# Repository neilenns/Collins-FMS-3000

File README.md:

# Collins-FMS-3000
PCB for a replica Collins FMS-3000 to use with MobiFlight

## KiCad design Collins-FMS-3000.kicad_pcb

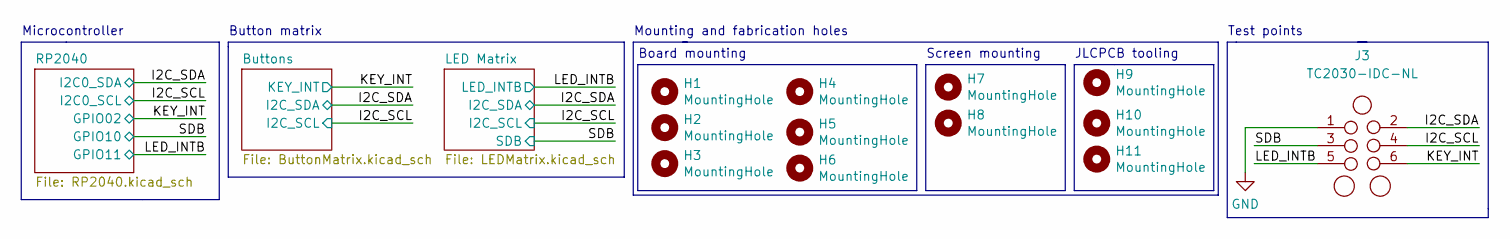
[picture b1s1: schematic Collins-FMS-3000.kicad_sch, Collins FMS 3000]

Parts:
H1, H2, H3, H4, H5, H6, H7, H8: MountingHole; MountingHole_3.2mm_M3
H9, H10, H11: MountingHole; JLCPCB_Tooling_Hole
J3: TC2030-IDC-NL; Tag-Connect_TC2030-IDC-NL_2x03_P1.27mm_Vertical

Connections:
/I2C_SCL: J3.4; also elsewhere on the board
/I2C_SDA: J3.2; also elsewhere on the board
/KEY_INT: J3.6; also elsewhere on the board
/LED_INTB: J3.5; also elsewhere on the board
/SDB: J3.3; also elsewhere on the board
GND: J3.1; also elsewhere on the board

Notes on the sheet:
Test points
Button matrix
Board mounting
Screen mounting
Microcontroller
Mounting and fabrication holes
JLCPCB tooling

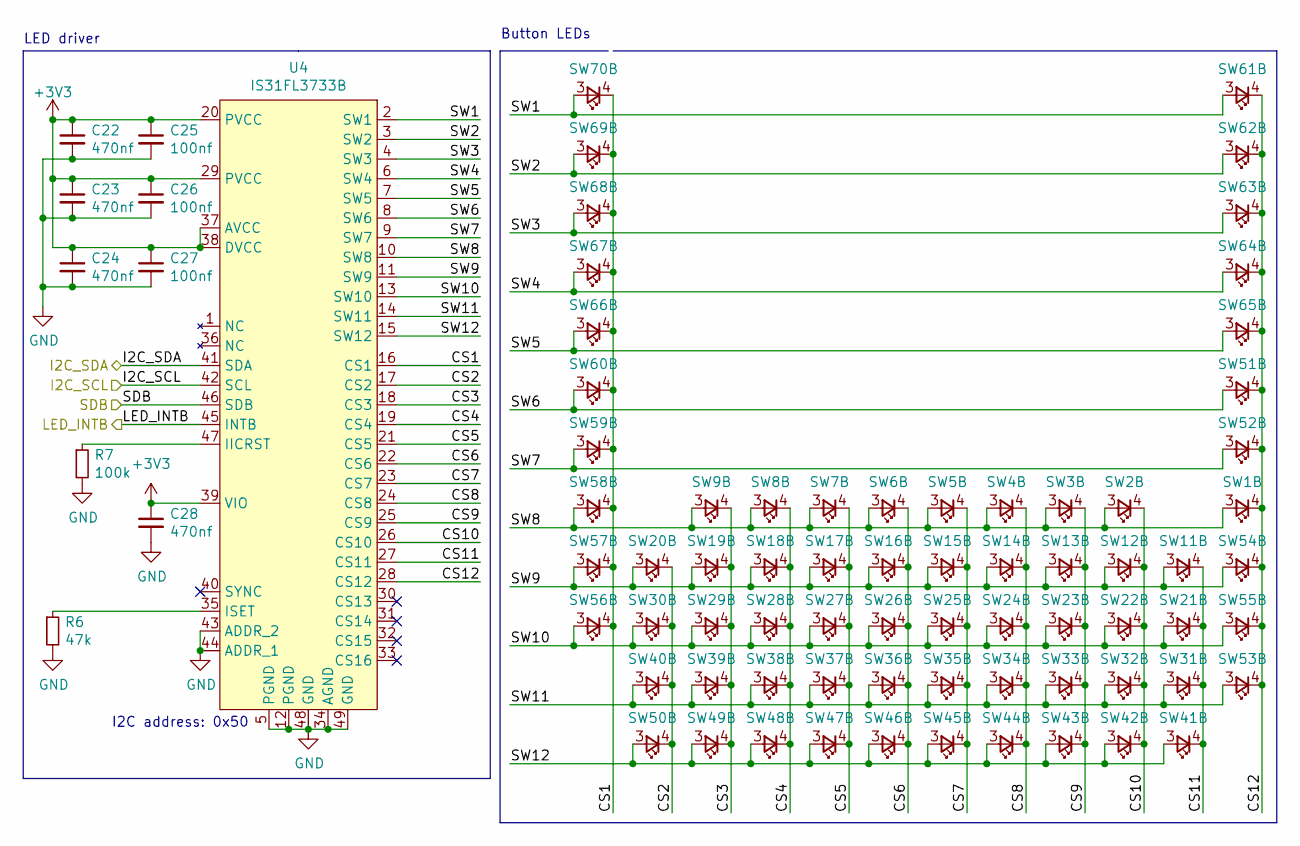
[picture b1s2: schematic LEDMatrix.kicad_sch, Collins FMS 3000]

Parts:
C22, C23, C24, C28: 470nf; Perfect_0402; MPN - JLCPCB C47339; JLC 0402
C25, C26, C27: 100nf; Perfect_0402; MPN - JLCPCB C1525; JLC 0402
R6: 47k; Perfect_0402; MPN - JLCPCB C25792; JLC 0402
R7: 100k; R_0603_1608Metric; MPN - JLCPCB C25803; JLC 0603
SW1, SW2, SW3, SW4, SW5, SW6, SW7, SW8, SW9, SW11, SW12, SW13, SW14, SW15, SW16, SW17, SW18, SW19, SW20, SW21, SW22, SW23, SW24, SW25, SW26, SW27, SW28, SW29, SW30, SW31, SW32, SW33, SW34, SW35, SW36, SW37, SW38, SW39, SW40, SW41, SW42, SW43, SW44, SW45, SW46, SW47, SW48, SW49, SW50, SW51, SW52, SW53, SW54, SW55, SW56, SW57, SW58, SW59, SW60, SW61, SW62, SW63, SW64, SW65, SW66, SW67, SW68, SW69, SW70: SW_Push_LED; SW_PUSH_LED_THT
U4: IS31FL3733B; TQFP-48-1EP_7x7mm_P0.5mm_EP5x5mm_ThermalVias

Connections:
+3V3: C22.1, C23.1, C24.1, C25.1, C26.1, C27.1, C28.1, U4.20 (PVCC), U4.29 (PVCC), U4.37 (AVCC), U4.38 (DVCC), U4.39 (VIO); also elsewhere on the board
/I2C_SCL: U4.42 (SCL); also elsewhere on the board
/I2C_SDA: U4.41 (SDA); also elsewhere on the board
/LED Matrix/CS1: SW56.4, SW57.4, SW58.4, SW59.4, SW60.4, SW66.4, SW67.4, SW68.4, SW69.4, SW70.4, U4.16 (CS1)
/LED Matrix/CS2: SW20.4, SW30.4, SW40.4, SW50.4, U4.17 (CS2)
/LED Matrix/CS3: SW9.4, SW19.4, SW29.4, SW39.4, SW49.4, U4.18 (CS3)
/LED Matrix/CS4: SW8.4, SW18.4, SW28.4, SW38.4, SW48.4, U4.19 (CS4)
/LED Matrix/CS5: SW7.4, SW17.4, SW27.4, SW37.4, SW47.4, U4.21 (CS5)
/LED Matrix/CS6: SW6.4, SW16.4, SW26.4, SW36.4, SW46.4, U4.22 (CS6)
/LED Matrix/CS7: SW5.4, SW15.4, SW25.4, SW35.4, SW45.4, U4.23 (CS7)
/LED Matrix/CS8: SW4.4, SW14.4, SW24.4, SW34.4, SW44.4, U4.24 (CS8)
/LED Matrix/CS9: SW3.4, SW13.4, SW23.4, SW33.4, SW43.4, U4.25 (CS9)
/LED Matrix/CS10: SW2.4, SW12.4, SW22.4, SW32.4, SW42.4, U4.26 (CS10)
/LED Matrix/CS11: SW11.4, SW21.4, SW31.4, SW41.4, U4.27 (CS11)
/LED Matrix/CS12: SW1.4, SW51.4, SW52.4, SW53.4, SW54.4, SW55.4, SW61.4, SW62.4, SW63.4, SW64.4, SW65.4, U4.28 (CS12)
/LED Matrix/SW1: SW61.3, SW70.3, U4.2 (SW1)
/LED Matrix/SW2: SW62.3, SW69.3, U4.3 (SW2)
/LED Matrix/SW3: SW63.3, SW68.3, U4.4 (SW3)
/LED Matrix/SW4: SW64.3, SW67.3, U4.6 (SW4)
/LED Matrix/SW5: SW65.3, SW66.3, U4.7 (SW5)
/LED Matrix/SW6: SW51.3, SW60.3, U4.8 (SW6)
/LED Matrix/SW7: SW52.3, SW59.3, U4.9 (SW7)
/LED Matrix/SW8: SW1.3, SW2.3, SW3.3, SW4.3, SW5.3, SW6.3, SW7.3, SW8.3, SW9.3, SW58.3, U4.10 (SW8)
/LED Matrix/SW9: SW11.3, SW12.3, SW13.3, SW14.3, SW15.3, SW16.3, SW17.3, SW18.3, SW19.3, SW20.3, SW54.3, SW57.3, U4.11 (SW9)
/LED Matrix/SW10: SW21.3, SW22.3, SW23.3, SW24.3, SW25.3, SW26.3, SW27.3, SW28.3, SW29.3, SW30.3, SW55.3, SW56.3, U4.13 (SW10)
/LED Matrix/SW11: SW31.3, SW32.3, SW33.3, SW34.3, SW35.3, SW36.3, SW37.3, SW38.3, SW39.3, SW40.3, SW53.3, U4.14 (SW11)
/LED Matrix/SW12: SW41.3, SW42.3, SW43.3, SW44.3, SW45.3, SW46.3, SW47.3, SW48.3, SW49.3, SW50.3, U4.15 (SW12)
/LED_INTB: U4.45 (INTB); also elsewhere on the board
/SDB: U4.46 (SDB); also elsewhere on the board
GND: C22.2, C23.2, C24.2, C25.2, C26.2, C27.2, C28.2, R6.2, R7.2, U4.5 (PGND), U4.12 (PGND), U4.34 (AGND), U4.43 (ADDR_2), U4.44 (ADDR_1), U4.48 (GND), U4.49 (GND); also elsewhere on the board
unnamed: R6.1, U4.35 (ISET)
unnamed: R7.1, U4.47 (IICRST)

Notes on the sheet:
LED driver
I2C address: 0x50
Button LEDs

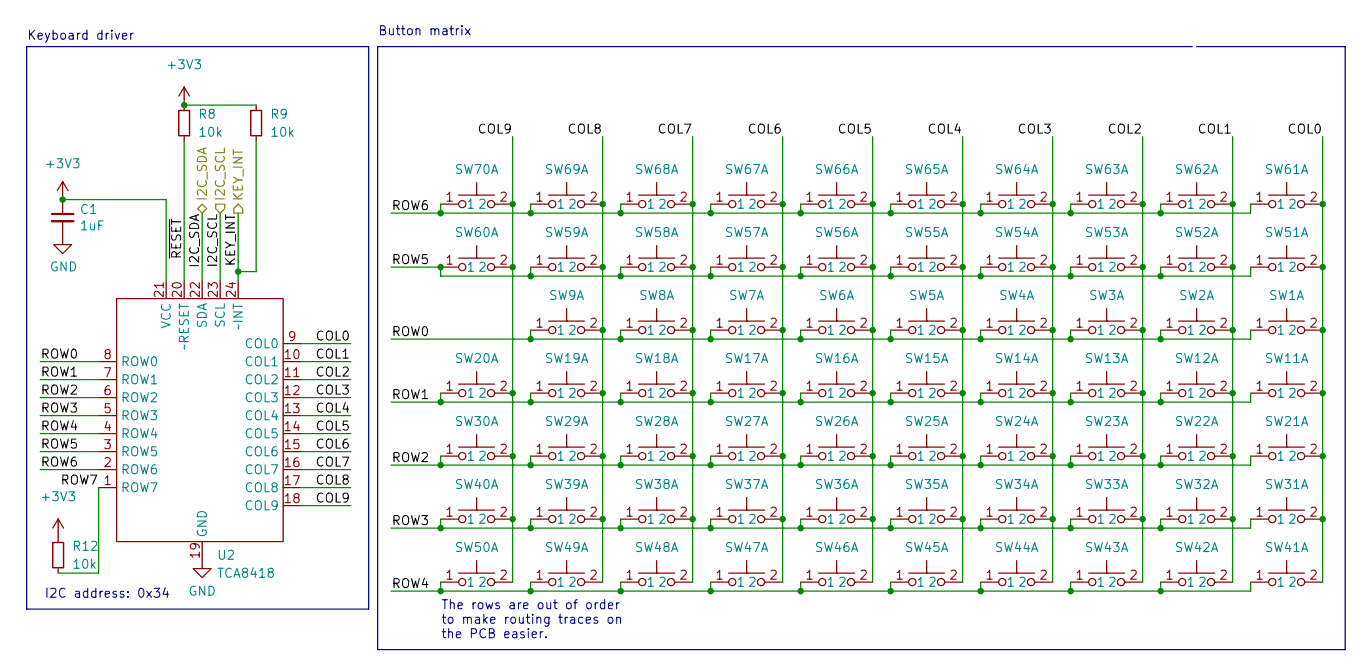
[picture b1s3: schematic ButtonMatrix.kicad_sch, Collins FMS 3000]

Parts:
C1: 1uF; Perfect_0402; MPN - JLCPCB C52923; JLC 0402
R8, R9, R12: 10k; Perfect_0402; MPN - JLCPCB C25744
SW1, SW2, SW3, SW4, SW5, SW6, SW7, SW8, SW9, SW11, SW12, SW13, SW14, SW15, SW16, SW17, SW18, SW19, SW20, SW21, SW22, SW23, SW24, SW25, SW26, SW27, SW28, SW29, SW30, SW31, SW32, SW33, SW34, SW35, SW36, SW37, SW38, SW39, SW40, SW41, SW42, SW43, SW44, SW45, SW46, SW47, SW48, SW49, SW50, SW51, SW52, SW53, SW54, SW55, SW56, SW57, SW58, SW59, SW60, SW61, SW62, SW63, SW64, SW65, SW66, SW67, SW68, SW69, SW70: SW_Push_LED; SW_PUSH_LED_THT
U2: TCA8418; WQFN-24-1EP_4x4mm_P0.5mm_EP2.6x2.6mm; MPN - JLCPCB C138713

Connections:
+3V3: C1.1, R8.1, R9.1, R12.1, U2.21 (VCC); also elsewhere on the board
/Buttons/COL0: SW1.2, SW11.2, SW21.2, SW31.2, SW41.2, SW51.2, SW61.2, U2.9 (COL0)
/Buttons/COL1: SW2.2, SW12.2, SW22.2, SW32.2, SW42.2, SW52.2, SW62.2, U2.10 (COL1)
/Buttons/COL2: SW3.2, SW13.2, SW23.2, SW33.2, SW43.2, SW53.2, SW63.2, U2.11 (COL2)
/Buttons/COL3: SW4.2, SW14.2, SW24.2, SW34.2, SW44.2, SW54.2, SW64.2, U2.12 (COL3)
/Buttons/COL4: SW5.2, SW15.2, SW25.2, SW35.2, SW45.2, SW55.2, SW65.2, U2.13 (COL4)
/Buttons/COL5: SW6.2, SW16.2, SW26.2, SW36.2, SW46.2, SW56.2, SW66.2, U2.14 (COL5)
/Buttons/COL6: SW7.2, SW17.2, SW27.2, SW37.2, SW47.2, SW57.2, SW67.2, U2.15 (COL6)
/Buttons/COL7: SW8.2, SW18.2, SW28.2, SW38.2, SW48.2, SW58.2, SW68.2, U2.16 (COL7)
/Buttons/COL8: SW9.2, SW19.2, SW29.2, SW39.2, SW49.2, SW59.2, SW69.2, U2.17 (COL8)
/Buttons/COL9: SW20.2, SW30.2, SW40.2, SW50.2, SW60.2, SW70.2, U2.18 (COL9)
/Buttons/ROW0: SW1.1, SW2.1, SW3.1, SW4.1, SW5.1, SW6.1, SW7.1, SW8.1, SW9.1, U2.8 (ROW0)
/Buttons/ROW1: SW11.1, SW12.1, SW13.1, SW14.1, SW15.1, SW16.1, SW17.1, SW18.1, SW19.1, SW20.1, U2.7 (ROW1)
/Buttons/ROW2: SW21.1, SW22.1, SW23.1, SW24.1, SW25.1, SW26.1, SW27.1, SW28.1, SW29.1, SW30.1, U2.6 (ROW2)
/Buttons/ROW3: SW31.1, SW32.1, SW33.1, SW34.1, SW35.1, SW36.1, SW37.1, SW38.1, SW39.1, SW40.1, U2.5 (ROW3)
/Buttons/ROW4: SW41.1, SW42.1, SW43.1, SW44.1, SW45.1, SW46.1, SW47.1, SW48.1, SW49.1, SW50.1, U2.4 (ROW4)
/Buttons/ROW5: SW51.1, SW52.1, SW53.1, SW54.1, SW55.1, SW56.1, SW57.1, SW58.1, SW59.1, SW60.1, U2.3 (ROW5)
/Buttons/ROW6: SW61.1, SW62.1, SW63.1, SW64.1, SW65.1, SW66.1, SW67.1, SW68.1, SW69.1, SW70.1, U2.2 (ROW6)
/Buttons/ROW7: R12.2, U2.1 (ROW7)
/Buttons/~RESET: R8.2, U2.20 (~RESET)
/I2C_SCL: U2.23 (SCL); also elsewhere on the board
/I2C_SDA: U2.22 (SDA); also elsewhere on the board
/KEY_INT: R9.2, U2.24 (~INT); also elsewhere on the board
GND: C1.2, U2.19 (GND); also elsewhere on the board

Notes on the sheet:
The rows are out of order to make routing traces on the PCB easier.
Button matrix
Keyboard driver
I2C address: 0x34

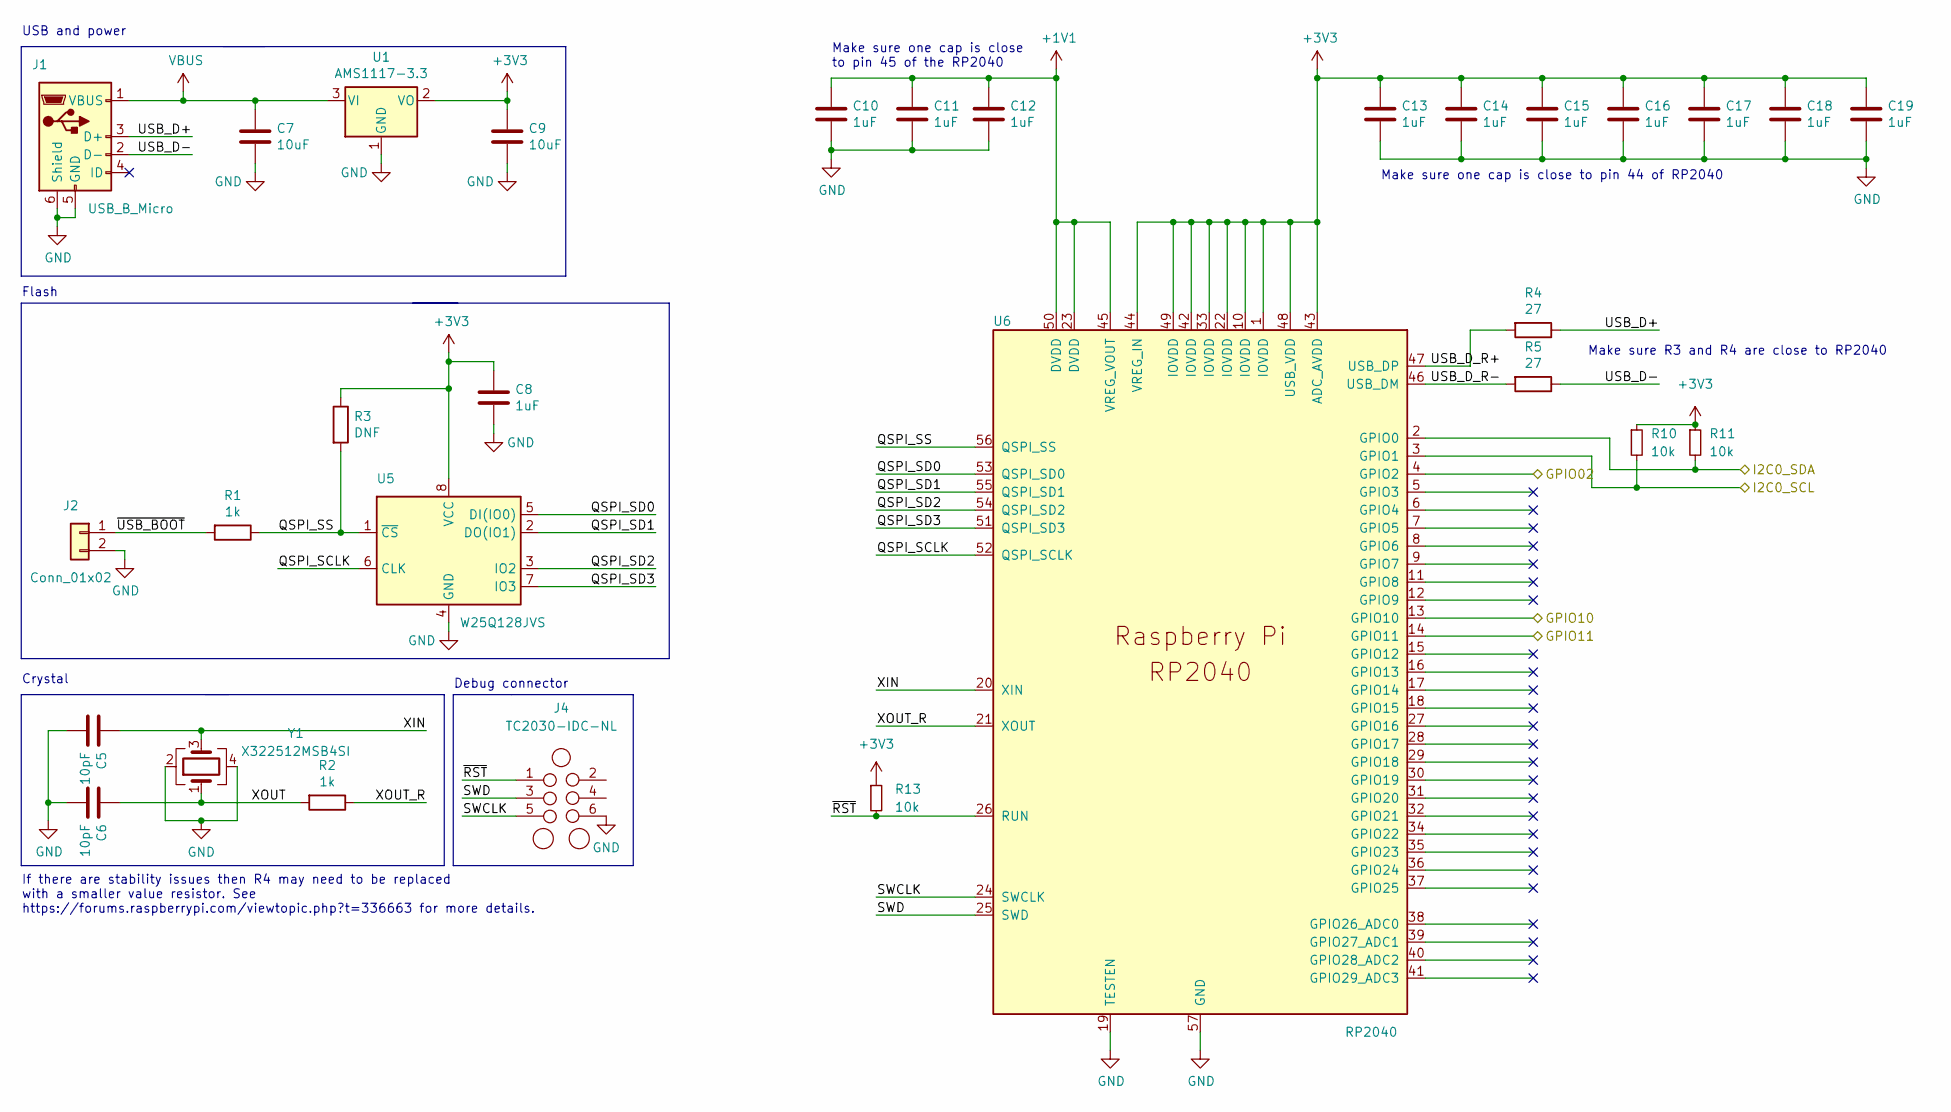
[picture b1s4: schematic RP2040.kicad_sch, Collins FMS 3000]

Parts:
C5, C6: 10pF; Perfect_0402; MPN - JLCPCB C32949; JLC 0402
C7, C9: 10uF; C_0603_1608Metric; MPN - JLCPCB C19702; JLC 0603
C8, C10, C11, C12, C13, C14, C15, C16, C17, C18, C19: 1uF; Perfect_0402; MPN - JLCPCB C52923; JLC 0402
J1: USB_B_Micro; USB_B_Mini_Amphenol_UE25BE5510H
J2: Conn_01x02; PinHeader_1x02_P2.54mm_Vertical
J4: TC2030-IDC-NL; Tag-Connect_TC2030-IDC-NL_2x03_P1.27mm_Vertical
R1, R2: 1k; Perfect_0402; MPN - JLCPCB C11702; JLC 0402
R3: DNF; R_1206_3216Metric_Pad1.30x1.75mm_HandSolder
R4, R5: 27; R_0603_1608Metric; MPN - JLCPCB C25190; JLC 0603
R10, R11: 10k; R_1206_3216Metric_Pad1.30x1.75mm_HandSolder; MPN - JLCPCB C17902
R13: 10k; Perfect_0402; MPN - JLCPCB C25744
U1: AMS1117-3.3; SOT-223-3_TabPin2; MPN - JLCPCB C6186; JLC SOT-223
U5: W25Q128JVS; SOIC-8_5.23x5.23mm_P1.27mm; MPN - JLCPCB C97521; JLC SOIC-8_5.3x5.3x1.27P
U6: RP2040; QFN56P40_700X700X90L40X18T310N; MPN - JLCPCB C2040; JLC LQFN-56_EP_7.0x7.0x0.4P
Y1: X322512MSB4SI; Crystal_SMD_3225-4Pin_3.2x2.5mm; MPN - JLCPCB C9002; JLC SMD-3225_4P

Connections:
+1V1: C10.1, C11.1, C12.1, U6.23 (DVDD), U6.45 (VREG_VOUT), U6.50 (DVDD)
+3V3: C8.1, C9.1, C13.1, C14.1, C15.1, C16.1, C17.1, C18.1, C19.1, R3.1, R10.1, R11.1, R13.1, U1.2 (VO), U5.8 (VCC), U6.1 (IOVDD), U6.10 (IOVDD), U6.22 (IOVDD), U6.33 (IOVDD), U6.42 (IOVDD), U6.43 (ADC_AVDD), U6.44 (VREG_IN), U6.48 (USB_VDD), U6.49 (IOVDD); also elsewhere on the board
/I2C_SCL: R10.2, U6.3 (GPIO1); also elsewhere on the board
/I2C_SDA: R11.2, U6.2 (GPIO0); also elsewhere on the board
/KEY_INT: U6.4 (GPIO2); also elsewhere on the board
/LED_INTB: U6.14 (GPIO11); also elsewhere on the board
/RP2040/QSPI_SCLK: U5.6 (CLK), U6.52 (QSPI_SCLK)
/RP2040/QSPI_SD0: U5.5 (DI(IO0)), U6.53 (QSPI_SD0)
/RP2040/QSPI_SD1: U5.2 (DO(IO1)), U6.55 (QSPI_SD1)
/RP2040/QSPI_SD2: U5.3 (IO2), U6.54 (QSPI_SD2)
/RP2040/QSPI_SD3: U5.7 (IO3), U6.51 (QSPI_SD3)
/RP2040/QSPI_SS: R1.1, R3.2, U5.1 (~CS), U6.56 (QSPI_SS)
/RP2040/SWCLK: J4.5, U6.24 (SWCLK)
/RP2040/SWD: J4.3, U6.25 (SWD)
/RP2040/USB_D+: J1.3 (D+), R4.1
/RP2040/USB_D-: J1.2 (D-), R5.1
/RP2040/USB_D_R+: R4.2, U6.47 (USB_DP)
/RP2040/USB_D_R-: R5.2, U6.46 (USB_DM)
/RP2040/XIN: C5.1, U6.20 (XIN), Y1.3
/RP2040/XOUT: C6.1, R2.2, Y1.1
/RP2040/XOUT_R: R2.1, U6.21 (XOUT)
/RP2040/~RST: J4.1, R13.2, U6.26 (RUN)
/RP2040/~USB_BOOT: J2.1, R1.2
/SDB: U6.13 (GPIO10); also elsewhere on the board
GND: C5.2, C6.2, C7.2, C8.2, C9.2, C10.2, C11.2, C12.2, C13.2, C14.2, C15.2, C16.2, C17.2, C18.2, C19.2, J1.5 (GND), J1.6 (Shield), J2.2, J4.6, U1.1 (GND), U5.4 (GND), U6.19 (TESTEN), U6.57 (GND), Y1.2, Y1.4; also elsewhere on the board
VBUS: C7.1, J1.1 (VBUS), U1.3 (VI)

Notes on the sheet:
USB and power
Crystal
Debug connector
Flash
If there are stability issues then R4 may need to be replaced with a smaller value resistor. See https://forums.raspberrypi.com/viewtopic.php?t=336663 for more details.
Make sure one cap is close to pin 45 of the RP2040
Make sure one cap is close to pin 44 of RP2040
Make sure R3 and R4 are close to RP2040

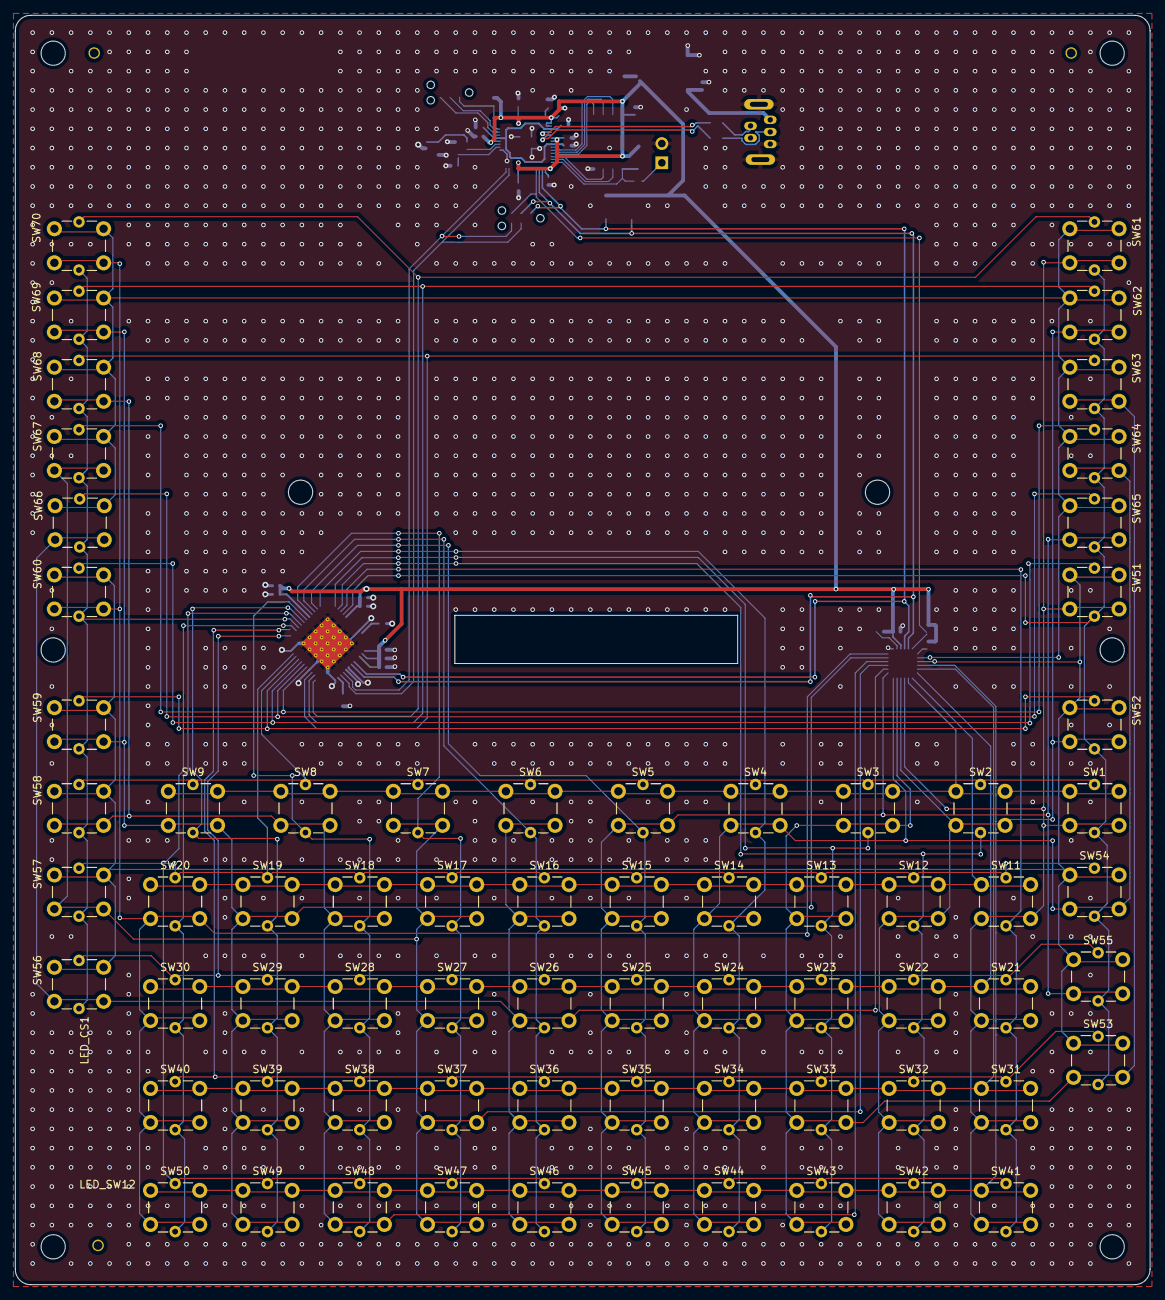
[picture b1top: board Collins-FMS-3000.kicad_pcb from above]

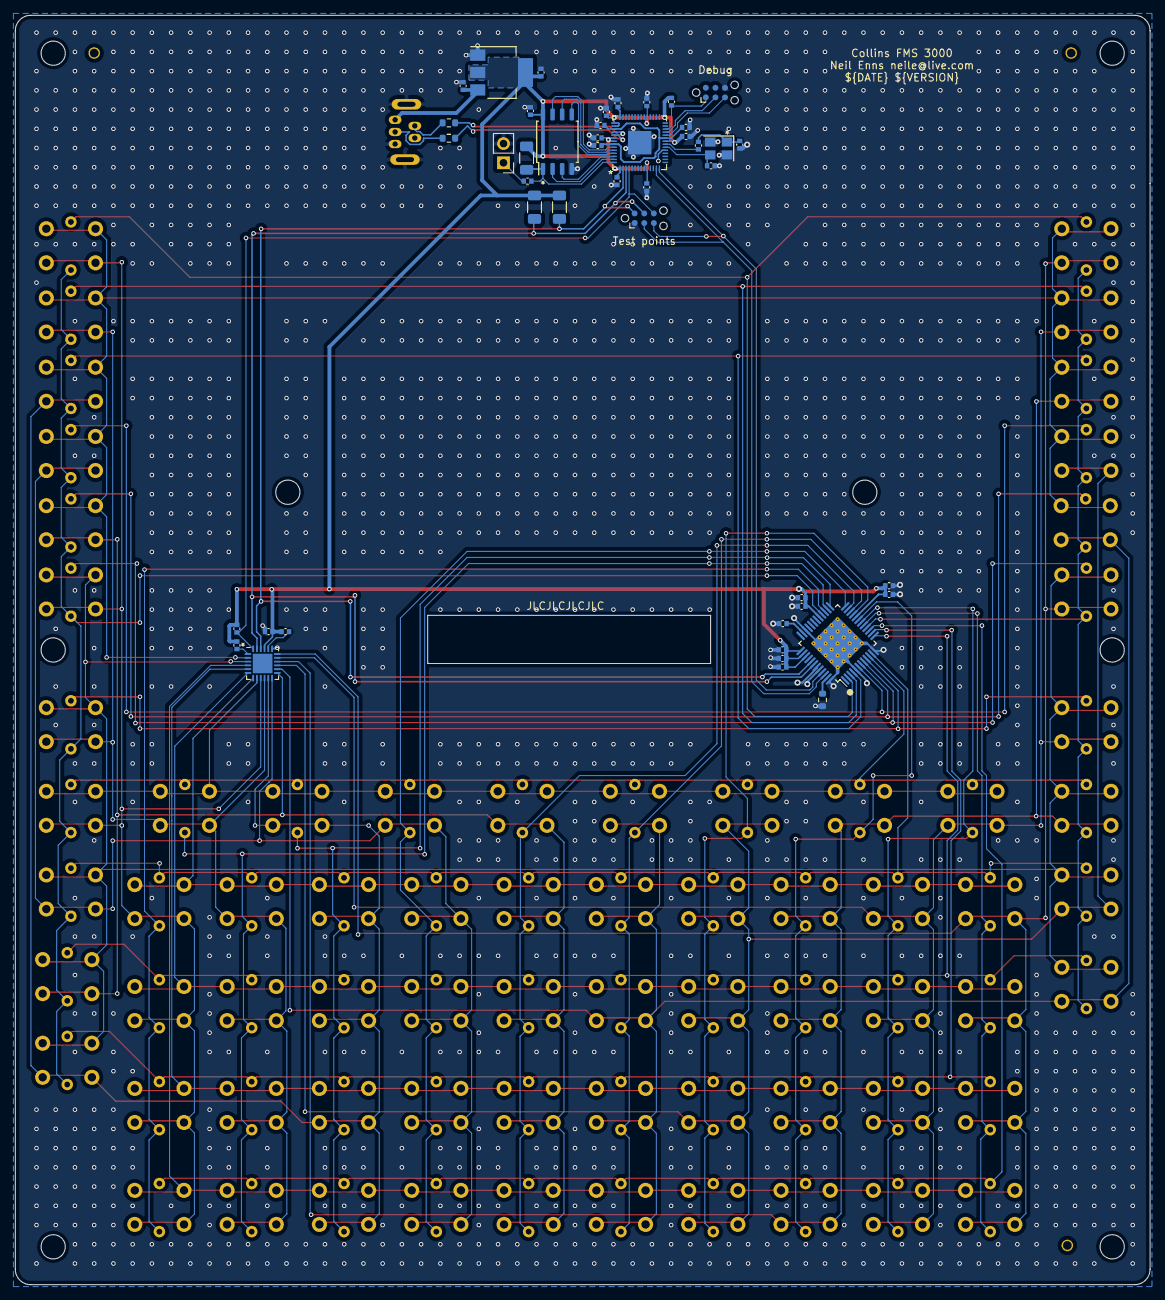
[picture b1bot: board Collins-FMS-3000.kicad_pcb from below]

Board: 2 copper layers, 149.9 x 167.6 mm, 126 parts (46 on the bottom side), 71 nets.

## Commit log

2021-11-03 Add KiCad gitignore
2021-11-03 Empty KiCad project
2021-11-03 Add CI/CD
2021-11-03 Initial button layout with IO expanders
2021-11-03 Change I2C address, add capacitors
2021-11-04 New component and key matrix done
2021-11-04 Schematic works
2021-11-08 Actual button matrix with sub sheets
2021-11-08 Fix KiBot action in release builds
2021-11-08 Add a generic PCB design so kibot runs
2021-11-08 Turn off ERC/DRC for now
2021-11-08 Remove MobiFlight zip from release builds
2021-11-08 Update variable placeholders
2021-11-08 Force v1 of find/replace
2021-11-08 Add LED driver chip
2021-11-08 Add LED driver and led matrix
2021-11-09 Add ATmega32u4 to board
2021-11-09 Redo the LED matrix
2021-11-09 Much PCB layout
2021-11-09 Lots of PCB layout
2021-11-10 Add footprint for IS31FL3733B
2021-11-10 New LED chip, tons of routing on the board
2021-11-10 Tons of PCB routing
2021-11-10 More routing
2021-11-11 Fully routed
2021-11-11 Fix some silkscreen
2021-11-11 Add mounting holes and silkscreen
2021-11-11 Assign JLCPCB part numbers
2021-11-11 Fix the button layout. Still needs trace work.
2021-11-11 Round edges, clean up traces, add placement marks
2021-11-11 Make github workflows generic
2021-11-11 Try using the repo name instead
2021-11-11 More action cleanup
2021-11-11 Comment and filename cleanup
2021-11-11 Get rid of BaseFileName in more places
2021-11-15 Add INTB connection
2021-11-18 Remove diodes, update interrupt connections
2021-11-20 Connect unused pins
2021-11-20 Get rid of interrupt pullups, add row pullups
2021-11-20 Attempt to fix two kibot bugs
2021-11-20 Fix yaml error
2021-11-20 Trying again
2021-11-20 Fix workflow naming bug
2021-11-20 Try fixing echo command
2021-11-20 Echo version
2021-11-20 Set environment variable correctly
2021-11-20 Continue on error and upload pcb file for inspection
2021-11-20 More continue on error
2021-11-20 Try PCB date replacement again
2021-11-20 Remove debugging stuff
2021-11-20 Fix github release version
2021-11-23 Add ROW INTB, new debug header
2021-11-28 Change ISET to 47k Fixes #3
2021-11-28 Connect thermal pad to ground pins Fixes #2
2021-11-28 Connect thermal pad to ground pins (#5)
2021-12-01 Fix pad clearence DRC errors
2021-12-01 Use perfect 0402 pad dimensions
2021-12-05 New PCB size and hole placement
2021-12-05 All buttons placed
2021-12-05 All buttons moved to new layout
2021-12-05 More trace routing
2021-12-06 MCPs are routed!
2021-12-06 Fully routed and passes DRC!
2021-12-06 Fix some bugs, add silkscreen
2021-12-06 Update components to match JLCPCB availability
2021-12-07 Add via stitching
2021-12-07 Fix JLCPCB part number for R28
2021-12-08 Minor schematic adjustment to clarify capacitor positions
2021-12-08 Minor schematic adjustment to clarify capacitor positions (#8)
2021-12-08 Switch to keystone test points
2021-12-08 Fix too close via DRC errors Fixes #11
2021-12-08 Fix too close via DRC errors (#12)
2021-12-08 Add keystone test points Fixes #9
2021-12-08 Add keystone test points (#13)
2022-01-11 Add version and date to PCB file Fixes #17
2022-01-11 Add version and date to PCB file (#18)
2022-01-11 Fix pull-up resistor value Fixes #14
2022-01-11 Fix pull-up resistor value (#19)
2022-01-11 Add keycaps
2022-01-11 Schematic update
2022-11-02 First pass trying to get the Pico done, plus obviously button caps
2022-11-02 Passes design rule checks
2022-11-02 Remove v5 files
2022-11-02 Switch to RP2040 instead of atmega32u4 (#21)
    * First pass trying to get the Pico done, plus obviously button caps
    * Passes design rule checks
    * Remove v5 files
2022-11-02 Fix placement of PCB version number
2022-11-02 Update kibot scripts and github actions
2022-11-02 Update silk screen to clarify pin 1 location on ICs
2022-11-02 Correct pin assignment for I2C, add via stitching
2022-11-02 Update button placement, board size, silkscreen, models
2022-11-02 JLCPCB rotation cleanup, kibot script fixes
2022-11-02 Fix version and date stamping
2022-11-02 Fix rotation for SOT-223-3_TabPin2
2022-11-03 Fix rotation *again*.
2022-11-03 Oh look. Another rotation update.
2022-11-03 Finally FINALLY fix rotation
2022-11-04 Update devcontainer to clone common components repo
2022-11-04 Switch to common component library USB connector
2022-11-04 First attempt at cloning custom component repo
2022-11-04 Fix workspace reference
2022-11-04 Trying quotes
2022-11-04 Try a different variable
2022-11-04 Try fixing this again
2022-11-04 Try removing the env
2022-11-04 Fix repository
2022-11-04 Try adding env.
2022-11-04 Try different {} format
2022-11-04 Update working directories
2022-11-04 Force stick main everywhere
2022-11-04 Try nested checkout instead
2022-11-04 Update action version
2022-11-04 Update documentation only action
2022-11-04 Add 3d rendering
2022-11-04 Fix casing
2022-11-04 Switch to new KiCad6 text variables for date and version
2022-11-04 Replace 6x6 buttons with common repo version
2022-11-11 Make a larger cutout for the display cable, add button cap designs
2022-11-11 Add test points
2022-11-12 Update button caps
2022-11-27 Final key caps
2022-12-11 Fix misaligned footprint
2023-01-05 Lots of pre-work before replacing RP2040 layout
2023-01-05 New RP2040 layout added
2023-01-05 Clean up schematic
2023-01-06 More trace cleanup
2023-01-06 Final trace cleanup
2023-01-06 Keyboard driver (#25)
    * Lots of pre-work before replacing RP2040 layout
    * New RP2040 layout added
    * FULLY ROUTED
    * Clean up schematic
    * More trace cleanup
    * Final trace cleanup
2023-01-06 Fix rotations again
2023-01-06 Oh look, another rotation fix.
2023-01-06 Add pin 1 indicator for keyboard driver
2023-01-06 Fix silkscreen, add via stitching
2023-01-06 Re-do vias, a bit less heavy this time.
2023-01-06 Redo the stitching again
2023-01-06 Clean up the schematic
2023-01-06 Renumber buttons to match key array position
2023-01-06 Renumber buttons to match key array position (#26)
2023-01-06 Add debug connector
2023-01-06 Add debug connector (#27)
2023-01-06 Oh wow, another rotation fix.
2023-01-07 Fix exposed pad warning
2023-01-21 Add via stitching (#29)
2025-02-25 Add renovate.json
